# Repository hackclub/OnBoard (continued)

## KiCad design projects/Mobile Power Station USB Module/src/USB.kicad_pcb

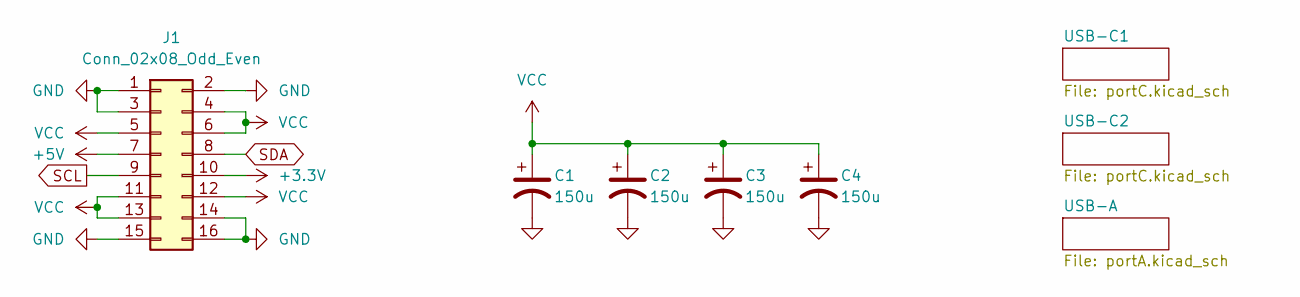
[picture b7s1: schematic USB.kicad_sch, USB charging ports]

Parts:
C1, C2, C3, C4: 150u; CP_Radial_D6.3mm_P2.50mm; LCSC Part C2976307
J1: Conn_02x08_Odd_Even; PinHeader_2x08_P2.54mm_Vertical

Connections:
+3.3V: J1.10
+5V: J1.7
GND: C1.2, C2.2, C3.2, C4.2, J1.1, J1.2, J1.3, J1.14, J1.15, J1.16; also elsewhere on the board
SCL: J1.9
SDA: J1.8
VCC: C1.1, C2.1, C3.1, C4.1, J1.4, J1.5, J1.6, J1.11, J1.12, J1.13; also elsewhere on the board

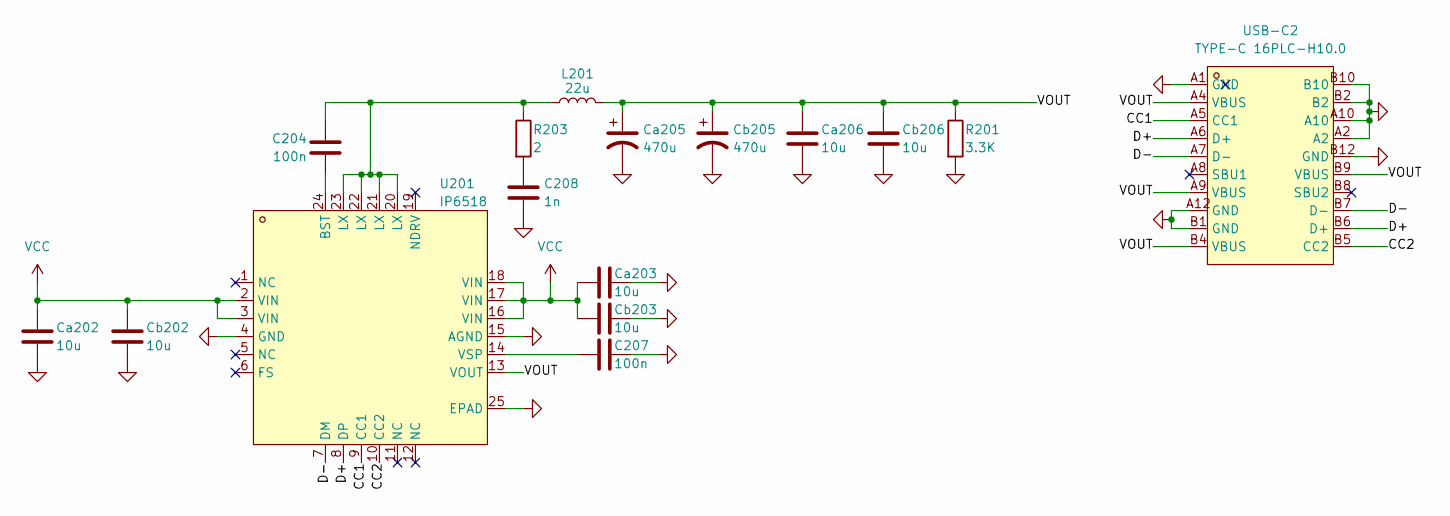
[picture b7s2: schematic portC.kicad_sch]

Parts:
C204, C207: 100n; C_0402_1005Metric
C208: 1n; C_0402_1005Metric
Ca202, Ca203, Ca206: 10u; C_1206_3216Metric; LCSC Part C13585
Ca205: 470u; CP_Radial_D10.0mm_P5.00mm; LCSC Part C2976267
Cb202, Cb203, Cb206: 10u; C_1206_3216Metric; LCSC Part C13585
Cb205: 470u; CP_Radial_D10.0mm_P5.00mm; LCSC Part C2976267
L201: 22u; IND-SMD_L13.5-W12.6_125CDMCC-DS; LCSC Part C357119
R201: 3.3K; R_0402_1005Metric
R203: 2; R_0402_1005Metric
U201: IP6518; QFN-24_L4.0-W4.0-P0.50-BL-EP2.6; LCSC Part C181688
USB-C2: TYPE-C 16PLC-H10.0; TYPE-C-TH_16PLC-H10.0; LCSC Part C3151747

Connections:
/USB-C2/CC1: U201.9 (CC1), USB-C2.A5 (CC1)
/USB-C2/CC2: U201.10 (CC2), USB-C2.B5 (CC2)
/USB-C2/D+: U201.8 (DP), USB-C2.A6 (D+), USB-C2.B6 (D+)
/USB-C2/D-: U201.7 (DM), USB-C2.A7 (D-), USB-C2.B7 (D-)
/USB-C2/VOUT: Ca205.1, Ca206.1, Cb205.1, Cb206.1, L201.2, R201.1, U201.13 (VOUT), USB-C2.A4 (VBUS), USB-C2.A9 (VBUS), USB-C2.B4 (VBUS), USB-C2.B9 (VBUS)
GND: C207.2, C208.1, Ca202.2, Ca203.2, Ca205.2, Ca206.2, Cb202.2, Cb203.2, Cb205.2, Cb206.2, R201.2, U201.4 (GND), U201.15 (AGND), U201.25 (EPAD), USB-C2.A1 (GND), USB-C2.A2, USB-C2.A10, USB-C2.A12 (GND), USB-C2.B1 (GND), USB-C2.B2, USB-C2.B10, USB-C2.B12 (GND); also elsewhere on the board
unnamed: C204.1, L201.1, R203.1, U201.20 (LX), U201.21 (LX), U201.22 (LX), U201.23 (LX)
unnamed: C208.2, R203.2
unnamed: C204.2, U201.24 (BST)
unnamed: C207.1, U201.14 (VSP)
VCC: Ca202.1, Ca203.1, Cb202.1, Cb203.1, U201.2 (VIN), U201.3 (VIN), U201.16 (VIN), U201.17 (VIN), U201.18 (VIN); also elsewhere on the board

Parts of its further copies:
C104, C107: 100n; C_0402_1005Metric
C108: 1n; C_0402_1005Metric
Ca102, Ca103, Ca106: 10u; C_1206_3216Metric; LCSC Part C13585
Ca105: 470u; CP_Radial_D10.0mm_P5.00mm; LCSC Part C2976267
Cb102, Cb103, Cb106: 10u; C_1206_3216Metric; LCSC Part C13585
Cb105: 470u; CP_Radial_D10.0mm_P5.00mm; LCSC Part C2976267
L101: 22u; IND-SMD_L13.5-W12.6_125CDMCC-DS; LCSC Part C357119
R101: 3.3K; R_0402_1005Metric
R103: 2; R_0402_1005Metric
U101: IP6518; QFN-24_L4.0-W4.0-P0.50-BL-EP2.6; LCSC Part C181688
USB-C1: TYPE-C 16PLC-H10.0; TYPE-C-TH_16PLC-H10.0; LCSC Part C3151747

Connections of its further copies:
/USB-C1/CC1: U101.9 (CC1), USB-C1.A5 (CC1)
/USB-C1/CC2: U101.10 (CC2), USB-C1.B5 (CC2)
/USB-C1/D+: U101.8 (DP), USB-C1.A6 (D+), USB-C1.B6 (D+)
/USB-C1/D-: U101.7 (DM), USB-C1.A7 (D-), USB-C1.B7 (D-)
/USB-C1/VOUT: Ca105.1, Ca106.1, Cb105.1, Cb106.1, L101.2, R101.1, U101.13 (VOUT), USB-C1.A4 (VBUS), USB-C1.A9 (VBUS), USB-C1.B4 (VBUS), USB-C1.B9 (VBUS)
GND: C107.2, C108.1, Ca102.2, Ca103.2, Ca105.2, Ca106.2, Cb102.2, Cb103.2, Cb105.2, Cb106.2, R101.2, U101.4 (GND), U101.15 (AGND), U101.25 (EPAD), USB-C1.A1 (GND), USB-C1.A2, USB-C1.A10, USB-C1.A12 (GND), USB-C1.B1 (GND), USB-C1.B2, USB-C1.B10, USB-C1.B12 (GND); also elsewhere on the board
unnamed: C104.1, L101.1, R103.1, U101.20 (LX), U101.21 (LX), U101.22 (LX), U101.23 (LX)
unnamed: C108.2, R103.2
unnamed: C104.2, U101.24 (BST)
unnamed: C107.1, U101.14 (VSP)
VCC: Ca102.1, Ca103.1, Cb102.1, Cb103.1, U101.2 (VIN), U101.3 (VIN), U101.16 (VIN), U101.17 (VIN), U101.18 (VIN); also elsewhere on the board

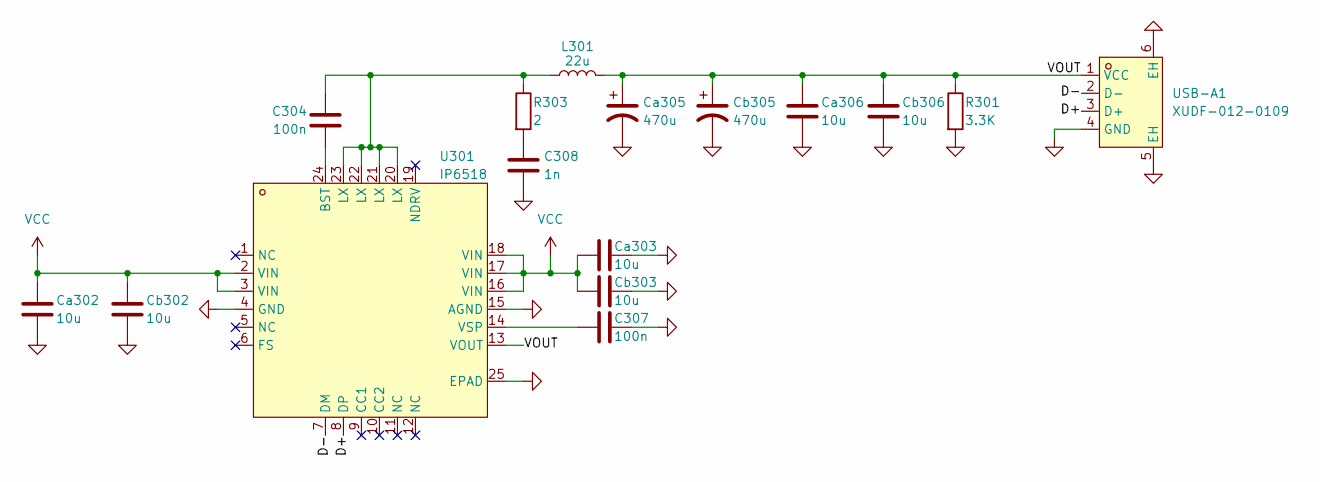
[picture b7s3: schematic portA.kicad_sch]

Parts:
C304, C307: 100n; C_0402_1005Metric
C308: 1n; C_0402_1005Metric
Ca302, Ca303, Ca306: 10u; C_1206_3216Metric; LCSC Part C13585
Ca305: 470u; CP_Radial_D10.0mm_P5.00mm; LCSC Part C2976267
Cb302, Cb303, Cb306: 10u; C_1206_3216Metric; LCSC Part C13585
Cb305: 470u; CP_Radial_D10.0mm_P5.00mm; LCSC Part C2976267
L301: 22u; IND-SMD_L13.5-W12.6_125CDMCC-DS; LCSC Part C357119
R301: 3.3K; R_0402_1005Metric
R303: 2; R_0402_1005Metric
U301: IP6518; QFN-24_L4.0-W4.0-P0.50-BL-EP2.6; LCSC Part C181688
USB-A1: XUDF-012-0109; USB-A-TH_XUDF-012-0109; LCSC Part C7529549

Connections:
/USB-A/D+: U301.8 (DP), USB-A1.3 (D+)
/USB-A/D-: U301.7 (DM), USB-A1.2 (D-)
/USB-A/VOUT: Ca305.1, Ca306.1, Cb305.1, Cb306.1, L301.2, R301.1, U301.13 (VOUT), USB-A1.1 (VCC)
GND: C307.2, C308.1, Ca302.2, Ca303.2, Ca305.2, Ca306.2, Cb302.2, Cb303.2, Cb305.2, Cb306.2, R301.2, U301.4 (GND), U301.15 (AGND), U301.25 (EPAD), USB-A1.4 (GND), USB-A1.5 (EH), USB-A1.6 (EH); also elsewhere on the board
unnamed: C304.1, L301.1, R303.1, U301.20 (LX), U301.21 (LX), U301.22 (LX), U301.23 (LX)
unnamed: C308.2, R303.2
unnamed: C304.2, U301.24 (BST)
unnamed: C307.1, U301.14 (VSP)
VCC: Ca302.1, Ca303.1, Cb302.1, Cb303.1, U301.2 (VIN), U301.3 (VIN), U301.16 (VIN), U301.17 (VIN), U301.18 (VIN); also elsewhere on the board

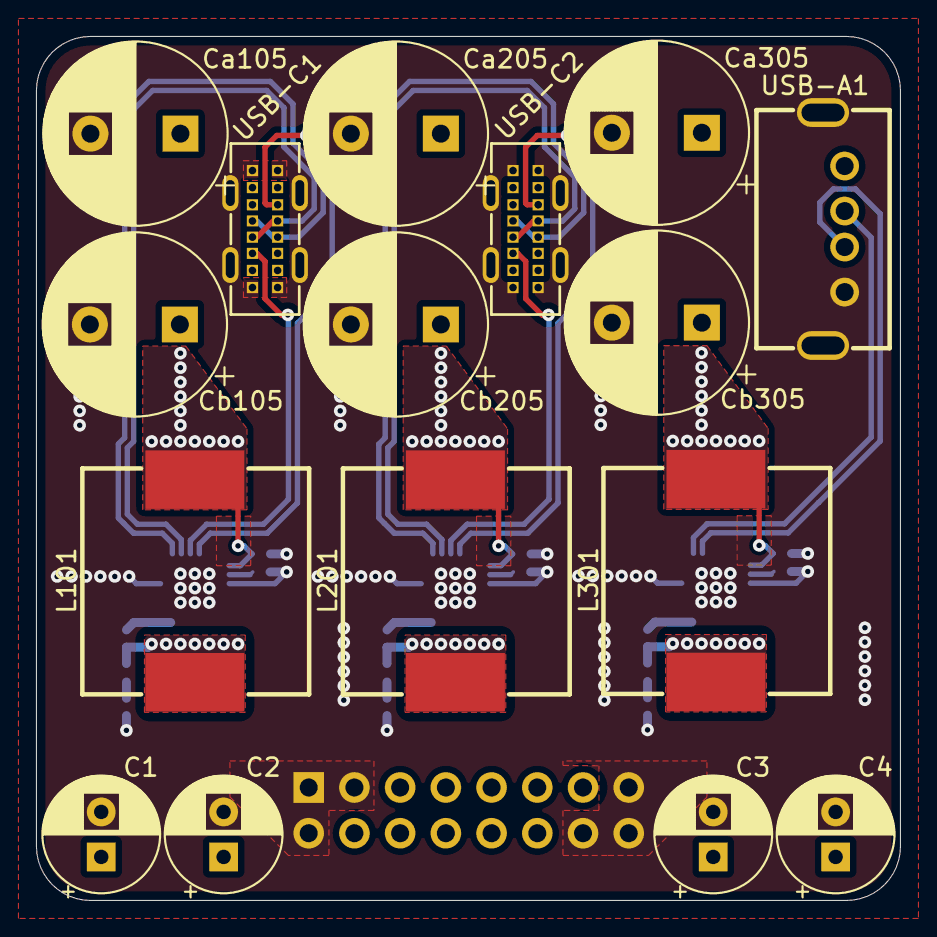
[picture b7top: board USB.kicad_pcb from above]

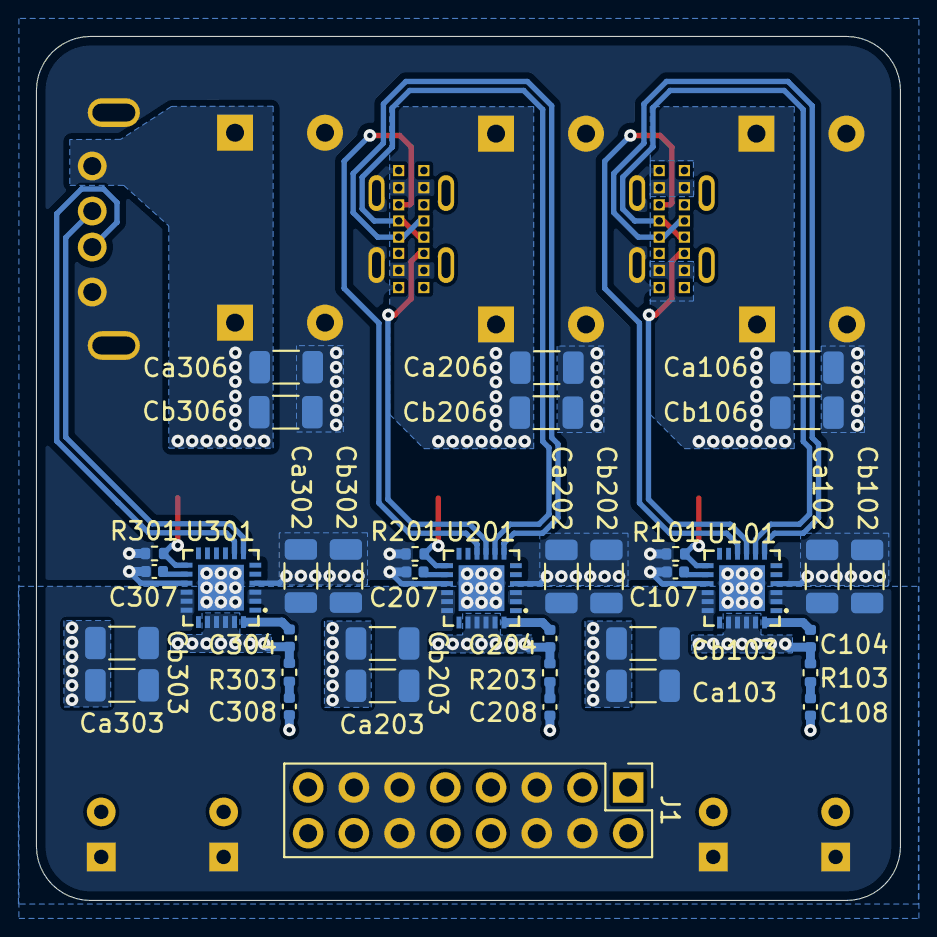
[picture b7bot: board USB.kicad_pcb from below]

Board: 2 copper layers, 48.0 x 48.0 mm, 53 parts (37 on the bottom side), 27 nets.

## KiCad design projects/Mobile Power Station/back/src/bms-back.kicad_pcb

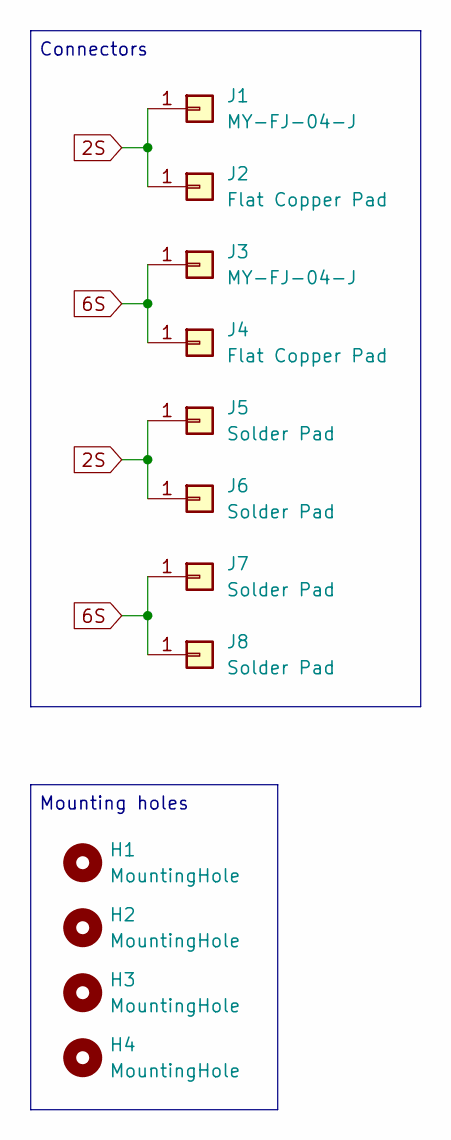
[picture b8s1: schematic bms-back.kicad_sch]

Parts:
H1, H2, H3, H4: MountingHole; MountingHole_3mm
J1, J3: MY-FJ-04-J; li-ion 21700 positive terminal contact; LCSC Part C5457115
J2, J4: Flat Copper Pad; li-ion 21700 negative terminal contact
J5, J6, J7, J8: Solder Pad; SolderWirePad_1x01_SMD_1x2mm

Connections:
2S: J1.1, J2.1, J5.1, J6.1
6S: J3.1, J4.1, J7.1, J8.1

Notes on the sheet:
Connectors
Mounting holes

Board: 2 copper layers, 12 parts (2 on the bottom side), 2 nets, no tracks yet.
